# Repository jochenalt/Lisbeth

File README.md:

# Lisbeth
Walter is a self-made, dangerous, industrial robot with 6 DOF. Right in the middle of development. Check the [Documentation](http://walter.readthedocs.io). Contact me via the [hackaday page](https://hackaday.io/post/53678).

### Contents
    /controller  dry theory

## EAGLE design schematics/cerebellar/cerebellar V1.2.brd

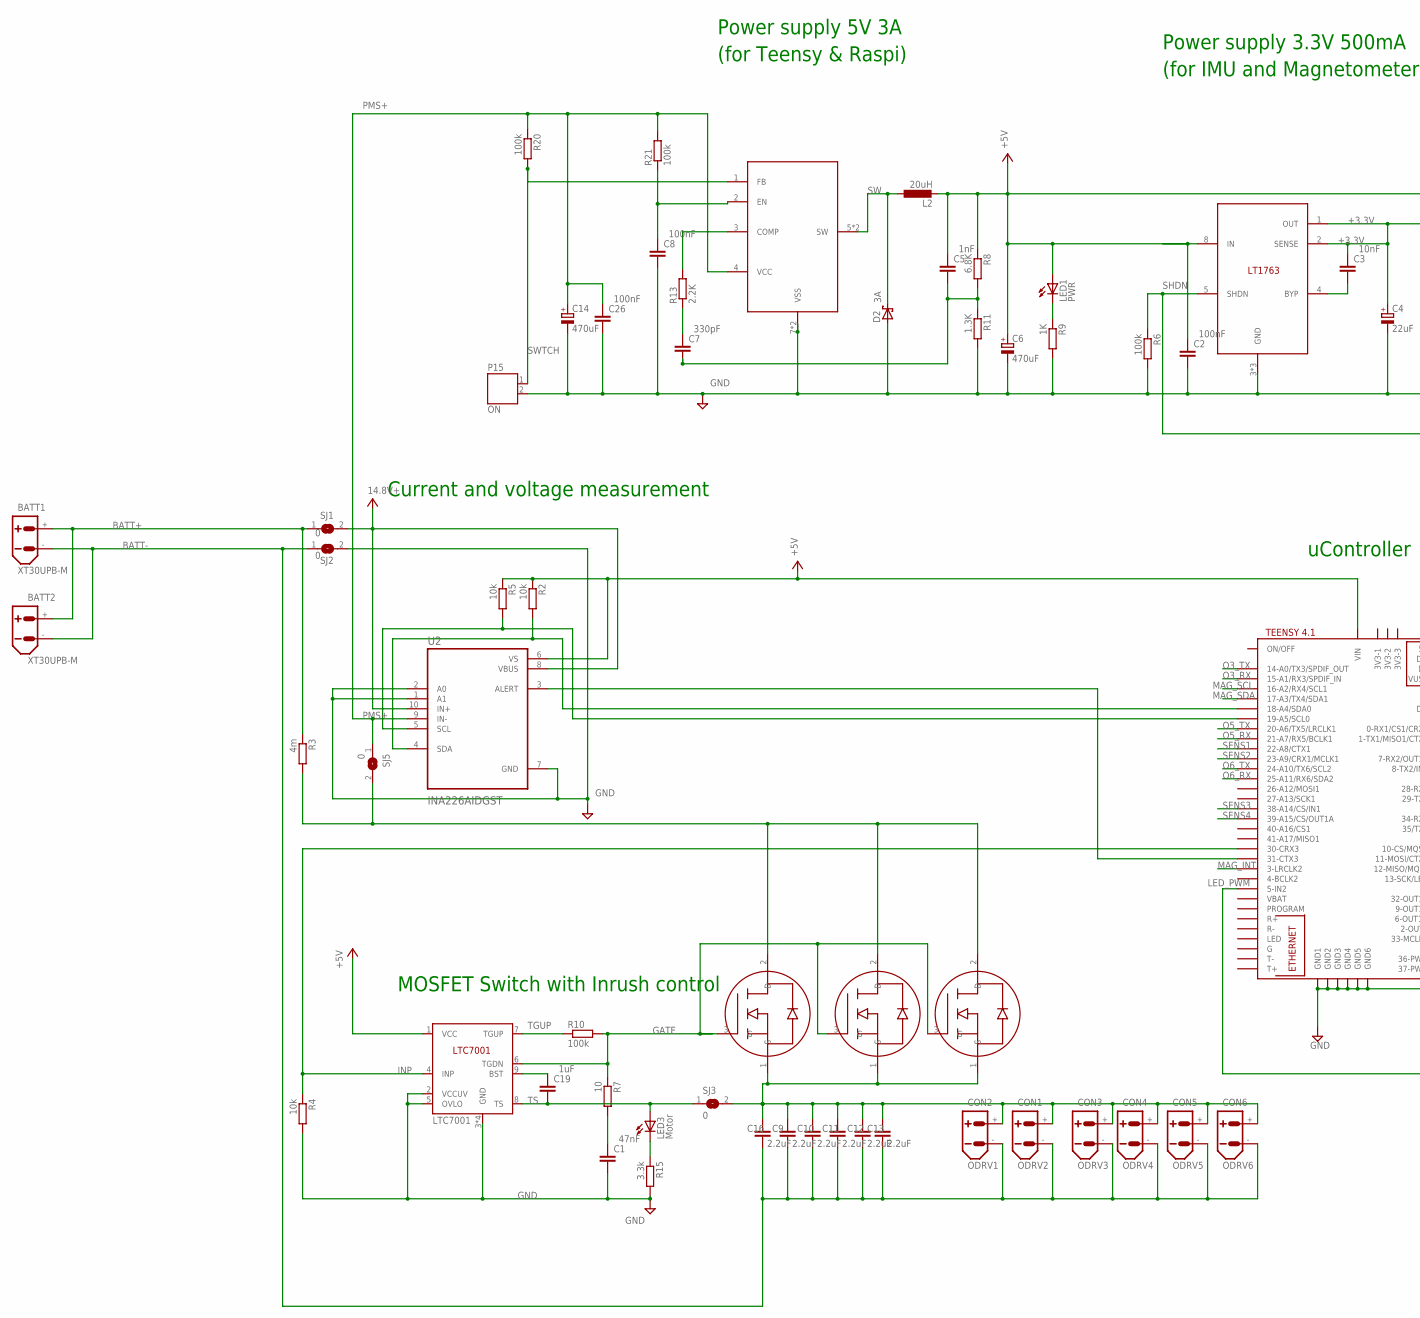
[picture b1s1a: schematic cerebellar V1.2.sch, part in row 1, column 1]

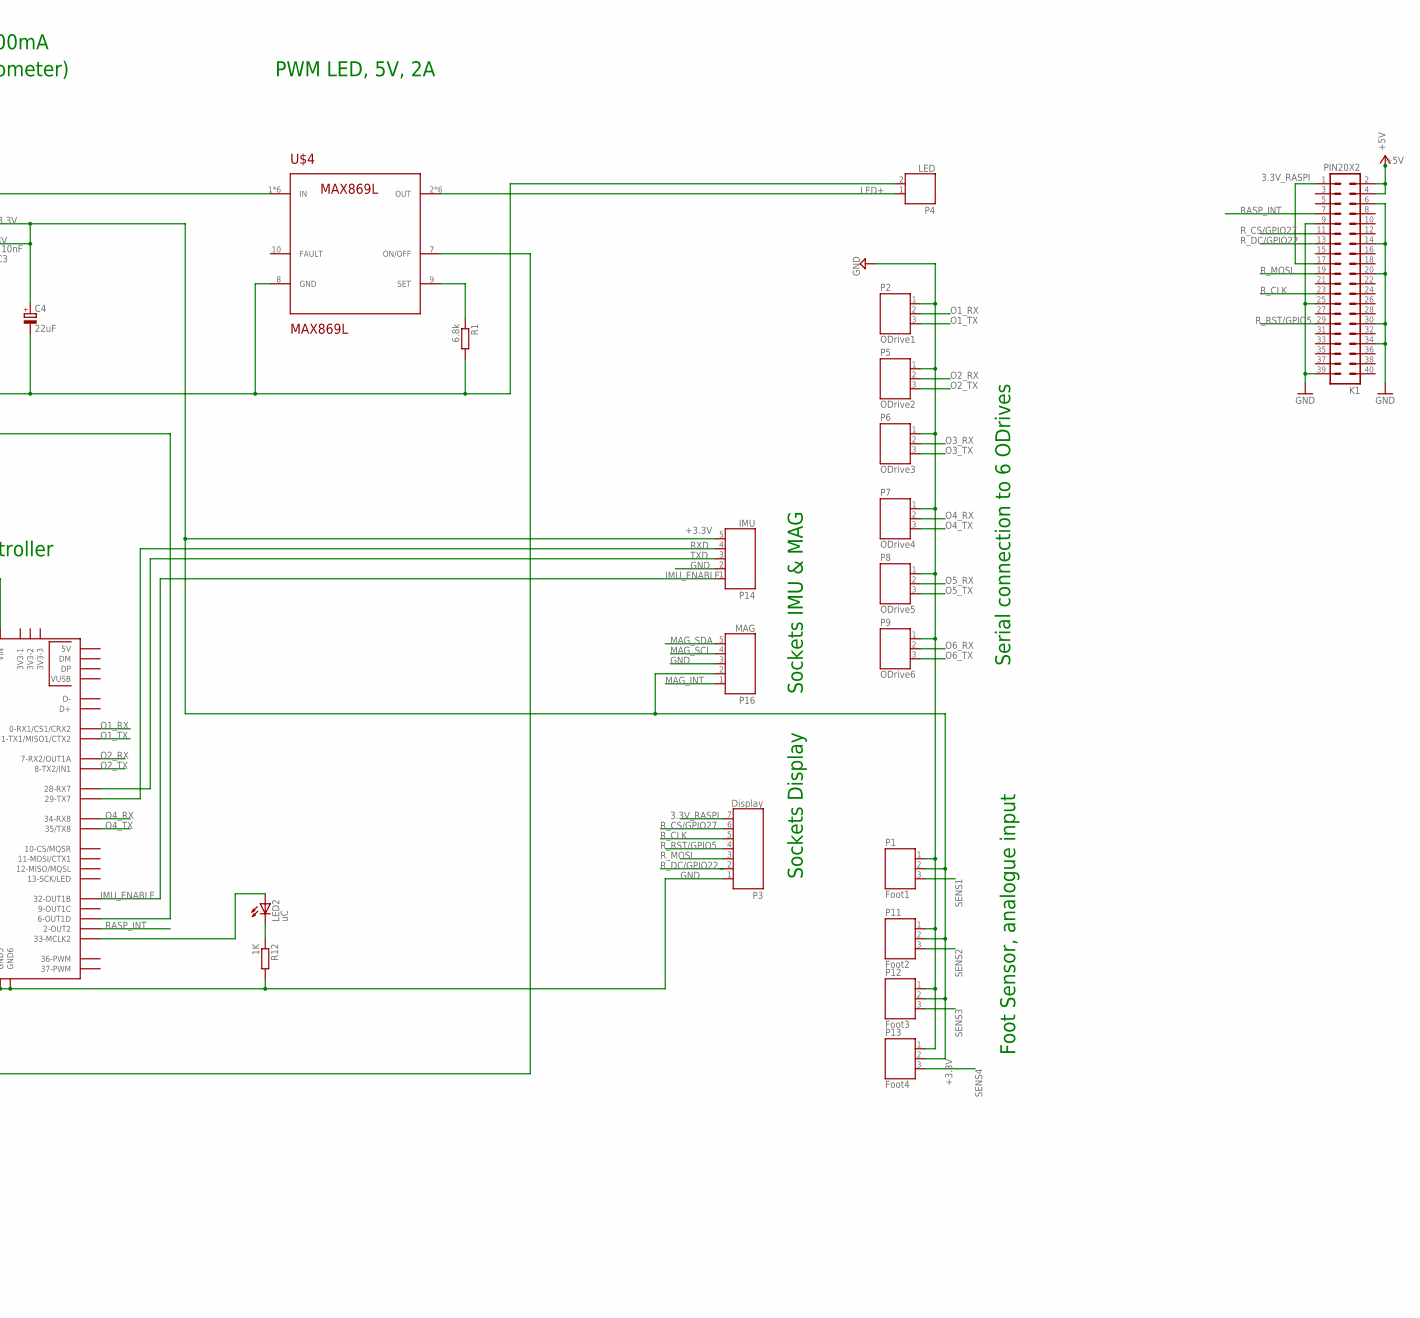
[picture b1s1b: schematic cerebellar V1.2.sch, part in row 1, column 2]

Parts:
BATT1, BATT2: XT30UPB-M
C1: 47nF; C050-024X044
C2, C8, C26: 100nF; C050-024X044
C3: 10nF; C050-024X044
C4: 22uF; E2-4
C5: 1nF; C050-024X044
C6, C14: 470uF; E2,5-6
C7: 330pF; C050-024X044
C9, C10, C11, C12, C13, C16: 2.2uF; C050-024X044
C19: 1uF; C050-024X044
CON1: ODRV2; XT30UPB-F
CON2: ODRV1; XT30UPB-F
CON3: ODRV3; XT30UPB-F
CON4: ODRV4; XT30UPB-F
CON5: ODRV5; XT30UPB-F
CON6: ODRV6; XT30UPB-F
D2: 3A; DO41-10
IC3: LTC7001; MSOP10
K1: PIN20X2; PIN_20X2
L2: 20uH; IRF-3
LED1: PWR; LED3MM
LED2: uC; LED3MM
LED3: Motor; LED3MM
P1: Foot1; JST-PH3
P2: ODrive1; JST-PH3
P3: Display; JST-PH7
P4: LED; JST-PH2
P5: ODrive2; JST-PH3
P6: ODrive3; JST-PH3
P7: ODrive4; JST-PH3
P8: ODrive5; JST-PH3
P9: ODrive6; JST-PH3
P11: Foot2; JST-PH3
P12: Foot3; JST-PH3
P13: Foot4; JST-PH3
P14: IMU; JST-PH5
P15: ON; JST-PH2
P16: MAG; JST-PH5
R1: 6.8k; 0204/7
R2, R4, R5: 10k; 0204/7
R3: 4m; R2512; DIGIKEY 541-WSK25124L000FEACT-ND
R6, R10, R20, R21: 100k; 0204/7
R7: 10; 0204/7
R8: 6.8K; 0204/7
R9, R12: 1K; 0204/7
R11: 1.3K; 0204/7
R13: 2.2K; 0204/7
R15: 3.3k; 0204/7
SJ1, SJ2, SJ3, SJ5: 0; SJ
U2: INA226AIDGST; SOP50P490X110-10N
U$1: TEENSY41
U$2, U$3, U$5: IRF2804-BACK; TO-220H-BACK
U$4: MAX869L; TSSOP-16
U$6: TS2509; SO08
U$8: LT1763; SO08

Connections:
3.3V_RASPI: K1.1, K1.17, P3.7
+3.3V: C3.1, C4.+, P1.2, P11.2, P12.2, P13.2, P14.5, P16.2, U$8.1 (OUT), U$8.2 (SENSE)
+5V: C2.1, C5.1, C6.+, IC3.1 (VCC), K1.2, K1.4, L2.2, LED1.A, R2.1, R5.1, R8.1, U2.6 (VS), U$1.VIN, U$4.1 (IN), U$4.4 (IN), U$4.5 (IN), U$4.12 (IN), U$4.13 (IN), U$4.16 (IN), U$8.8 (IN)
BATT+: BATT1.+, BATT2.+, R3.1, SJ1.1
BATT-: BATT1.-, BATT2.-, C9.2, C10.2, C11.2, C12.2, C13.2, C16.2, CON1.-, CON2.-, CON3.-, CON4.-, CON5.-, CON6.-, SJ2.1
DRAIN: R3.2, SJ5.2, U$2.2 (D), U$3.2 (D), U$5.2 (D)
GATE: IC3.6 (TGDN), R7.1, R10.2, U$2.3 (G), U$3.3 (G), U$5.3 (G)
GND: C1.2, C2.2, C4.-, C6.-, C8.2, C14.-, C26.2, D2.A, IC3.2 (VCCUV), IC3.3 (GND), IC3.5 (OVLO), IC3.10 (GND), IC3.11 (GND), IC3.12 (GND), K1.6, K1.9, K1.14, K1.20, K1.25, K1.30, K1.34, K1.39, P1.1, P2.1, P3.1, P4.2, P5.1, P6.1, P7.1, P8.1, P9.1, P11.1, P12.1, P13.1, P14.2, P15.2, P16.3, R1.2, R4.2, R6.2, R9.2, R11.2, R12.2, R15.2, SJ2.2, U2.1 (A1), U2.2 (A0), U2.7 (GND), U$1.GND1, U$1.GND2, U$1.GND3, U$1.GND4, U$1.GND5, U$1.GND6, U$4.8 (GND), U$6.7 (VSS), U$6.8 (VSS), U$8.3 (GND), U$8.6 (GND), U$8.7 (GND)
IMU_ENABLE: P14.1, U$1.32-OUT1B
INP: IC3.4 (INP), R4.1, U$1.30-CRX3
LED+: P4.1, U$4.2 (OUT), U$4.3 (OUT), U$4.6 (OUT), U$4.11 (OUT), U$4.14 (OUT), U$4.15 (OUT)
LED_PWM: U$1.5-IN2, U$4.7 (ON/OFF)
MAG_INT: P16.1, U$1.3-LRCLK2
MAG_SCL: P16.4, U$1.16-A2/RX4/SCL1
MAG_SDA: P16.5, U$1.17-A3/TX4/SDA1
unnamed: C1.1, R7.2
unnamed: R1.1, U$4.9 (SET)
unnamed: LED2.K (C), R12.1
unnamed: LED2.A, U$1.33-MCLK2
unnamed: U2.3 (ALERT), U$1.31-CTX3
unnamed: C5.2, C7.2, R8.2, R11.1
unnamed: C3.2, U$8.4 (BYP)
unnamed: R13.2, U$6.3 (COMP)
unnamed: C7.1, R13.1
unnamed: R5.2, U2.5 (SCL), U$1.19-A5/SCL0
unnamed: R2.2, U2.4 (SDA), U$1.18-A4/SDA0
unnamed: C19.1, IC3.9 (BST)
unnamed: LED3.K (C), R15.1
unnamed: LED1.K (C), R9.1
unnamed: C8.1, R21.1, U$6.2 (EN)
O1_RX: P2.2, U$1.0-RX1/CS1/CRX2
O1_TX: P2.3, U$1.1-TX1/MISO1/CTX2
O2_RX: P5.2, U$1.7-RX2/OUT1A
O2_TX: P5.3, U$1.8-TX2/IN1
O3_RX: P6.2, U$1.15-A1/RX3/SPDIF_IN
O3_TX: P6.3, U$1.14-A0/TX3/SPDIF_OUT
O4_RX: P7.2, U$1.34-RX8
O4_TX: P7.3, U$1.35-TX8 (35/TX8)
O5_RX: P8.2, U$1.21-A7/RX5/BCLK1
O5_TX: P8.3, U$1.20-A6/TX5/LRCLK1
O6_RX: P9.2, U$1.25-A11/RX6/SDA2
O6_TX: P9.3, U$1.24-A10/TX6/SCL2
PMS+: C14.+, C26.1, R20.1, R21.2, SJ5.1, U2.9 (IN-), U$6.4 (VCC)
POWER+: C9.1, C10.1, C11.1, C12.1, C13.1, C16.1, CON1.+, CON2.+, CON3.+, CON4.+, CON5.+, CON6.+, SJ3.2, U$2.1 (S), U$3.1 (S), U$5.1 (S)
RASP_INT: K1.7, U$1.2-OUT2
RXD: P14.4, U$1.29-TX7
R_CLK: K1.23, P3.5
R_CS/GPIO27: K1.11, P3.6
R_DC/GPIO22: K1.13, P3.2
R_MOSI: K1.19, P3.3
R_RST/GPIO5: K1.29, P3.4
SENS1: P1.3, U$1.22-A8/CTX1
SENS2: P11.3, U$1.23-A9/CRX1/MCLK1
SENS3: P12.3, U$1.38-A14/CS/IN1
SENS4: P13.3, U$1.39-A15/CS/OUT1A
SHDN: R6.1, U$1.6-OUT1D, U$8.5 (SHDN)
SW: D2.C, L2.1, U$6.5 (SW), U$6.6 (SW)
SWTCH: P15.1, R20.2, U$6.1 (FB)
TGUP: IC3.7 (TGUP), R10.1
TS: C19.2, IC3.8 (TS), LED3.A, SJ3.1
TXD: P14.3, U$1.28-RX7
V+: SJ1.2, U2.8 (VBUS), U2.10 (IN+)

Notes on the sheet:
Foot Sensor, analogue input
Serial connection to 6 ODrives
Power supply 5V 3A (for Teensy & Raspi)
Current and voltage measurement
MOSFET Switch with Inrush control
uController
PWM LED, 5V, 2A
Power supply 3.3V 500mA (for IMU and Magnetometer)
Sockets IMU & MAG
Sockets Display

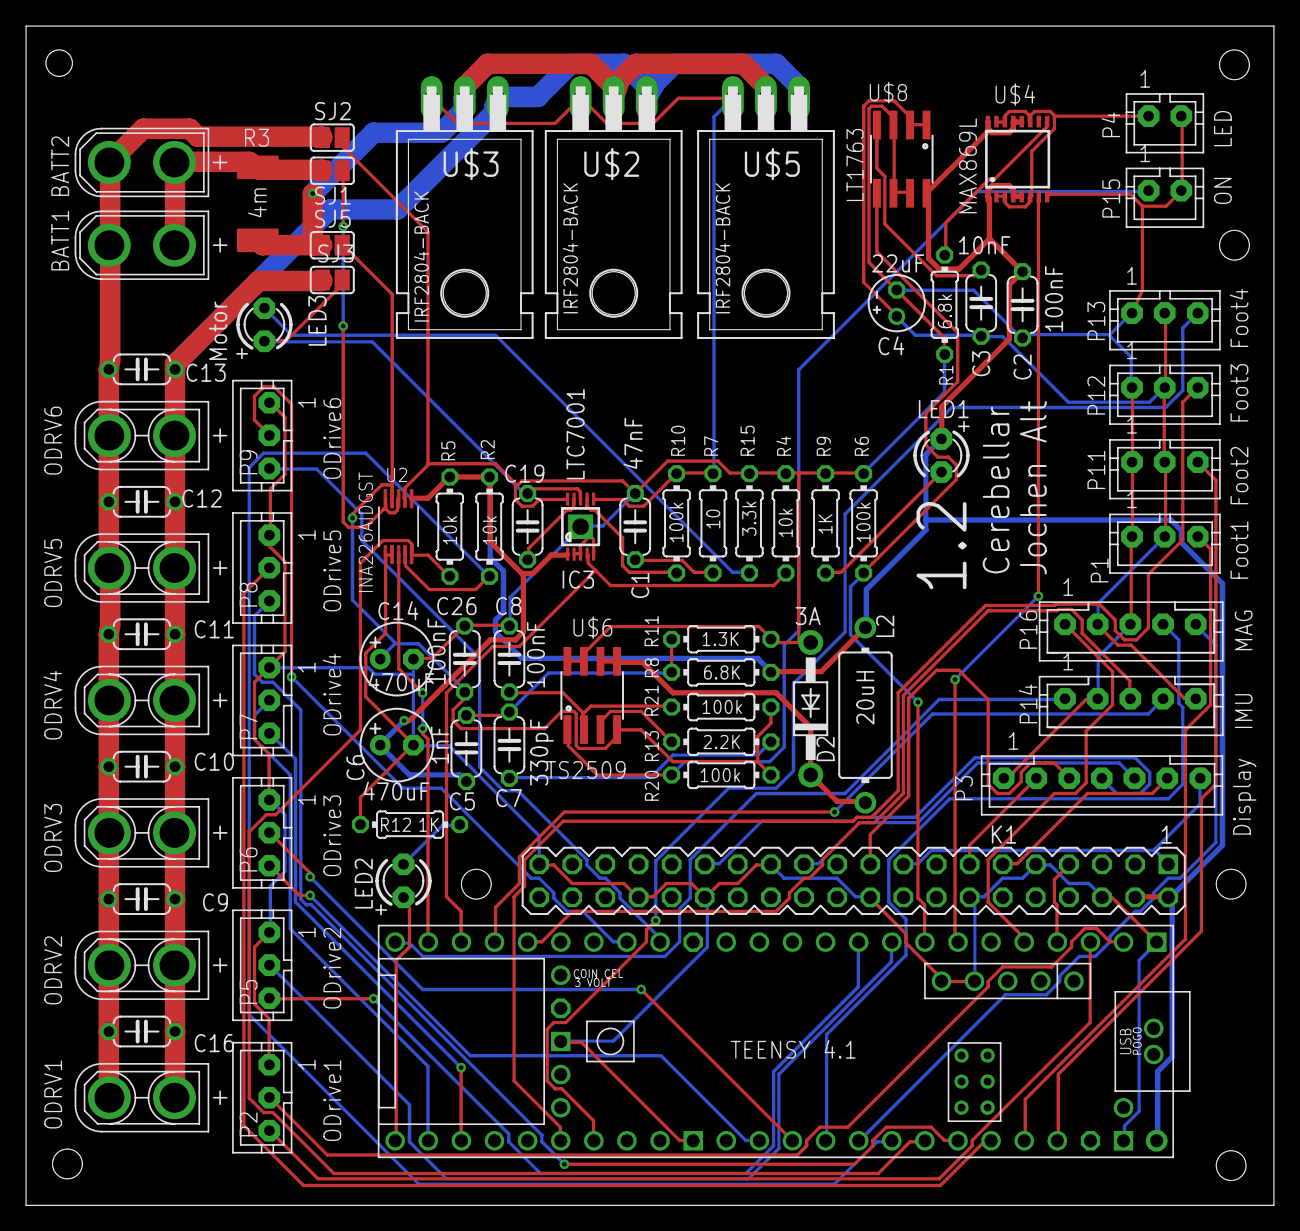
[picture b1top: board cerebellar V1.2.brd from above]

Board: 2 copper layers, 95.7 x 90.5 mm, 75 parts (0 on the bottom side), 62 nets.

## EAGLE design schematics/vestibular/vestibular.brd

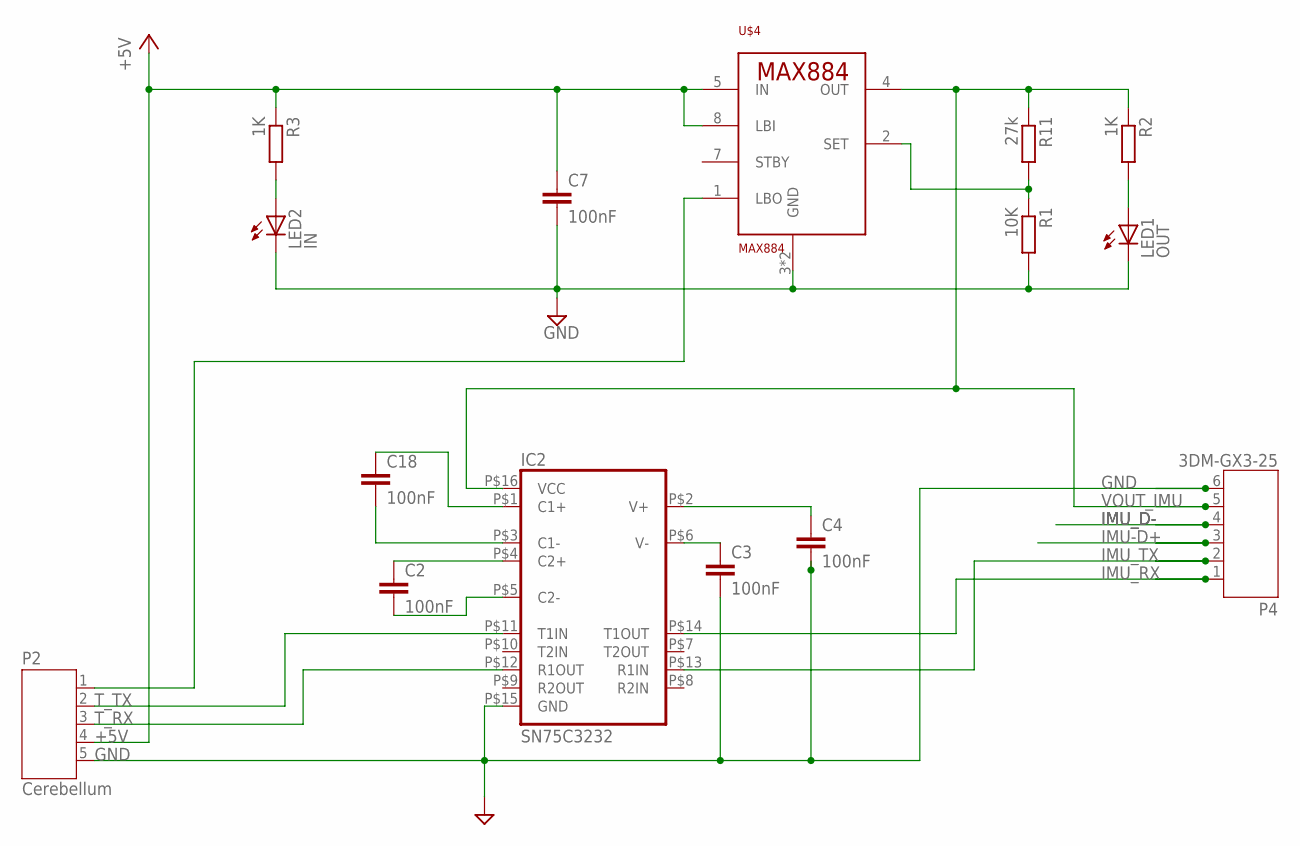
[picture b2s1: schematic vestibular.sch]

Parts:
C2, C3, C4, C7, C18: 100nF; C025-025X050
IC2: SN75C3232; SOIC16
LED1: OUT; LED3MM
LED2: IN; LED3MM
P2: Cerebellum; JST-PH5
P4: 3DM-GX3-25; JST-PH6
R1: 10K; 0204/7
R2, R3: 1K; 0204/7
R11: 27k; 0204/7
U$4: MAX884; SO08

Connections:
+5V: C7.1, P2.4, R3.1, U$4.5 (IN), U$4.8 (LBI)
GND: C3.2, C4.2, C7.2, IC2.P$15 (GND), LED1.K (C), LED2.K (C), P2.5, P4.6, R1.2, U$4.3 (GND), U$4.6 (GND)
IMU-D+: P4.3
IMU_D-: P4.4
IMU_RX: IC2.P$14 (T1OUT), P4.1
IMU_TX: IC2.P$13 (R1IN), P4.2
unnamed: LED1.A, R2.2
unnamed: LED2.A, R3.2
unnamed: C18.1, IC2.P$1 (C1+)
unnamed: P2.1, U$4.1 (LBO)
unnamed: C18.2, IC2.P$3 (C1-)
unnamed: R1.1, R11.2, U$4.2 (SET)
unnamed: C2.1, IC2.P$4 (C2+)
unnamed: C2.2, IC2.P$5 (C2-)
unnamed: C4.1, IC2.P$2 (V+)
unnamed: C3.1, IC2.P$6 (V-)
T_RX: IC2.P$12 (R1OUT), P2.3
T_TX: IC2.P$11 (T1IN), P2.2
VOUT_IMU: IC2.P$16 (VCC), P4.5, R2.1, R11.1, U$4.4 (OUT)

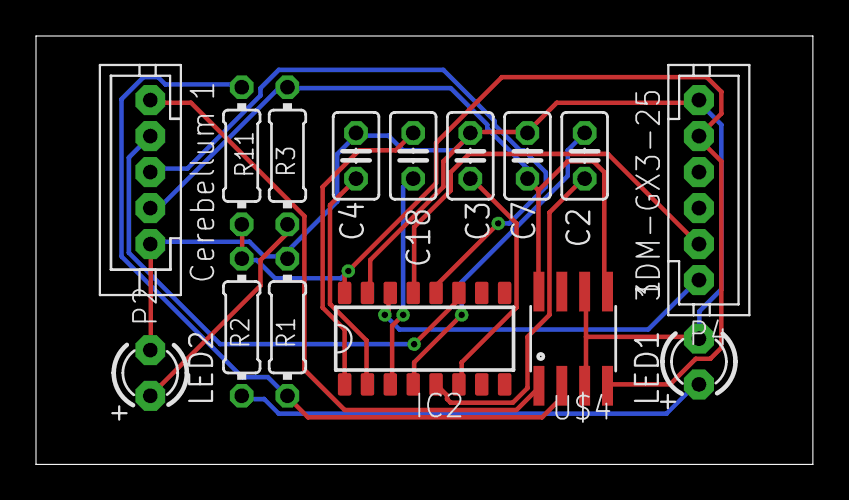
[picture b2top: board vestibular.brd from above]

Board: 2 copper layers, 43.2 x 23.8 mm, 15 parts (0 on the bottom side), 17 nets.

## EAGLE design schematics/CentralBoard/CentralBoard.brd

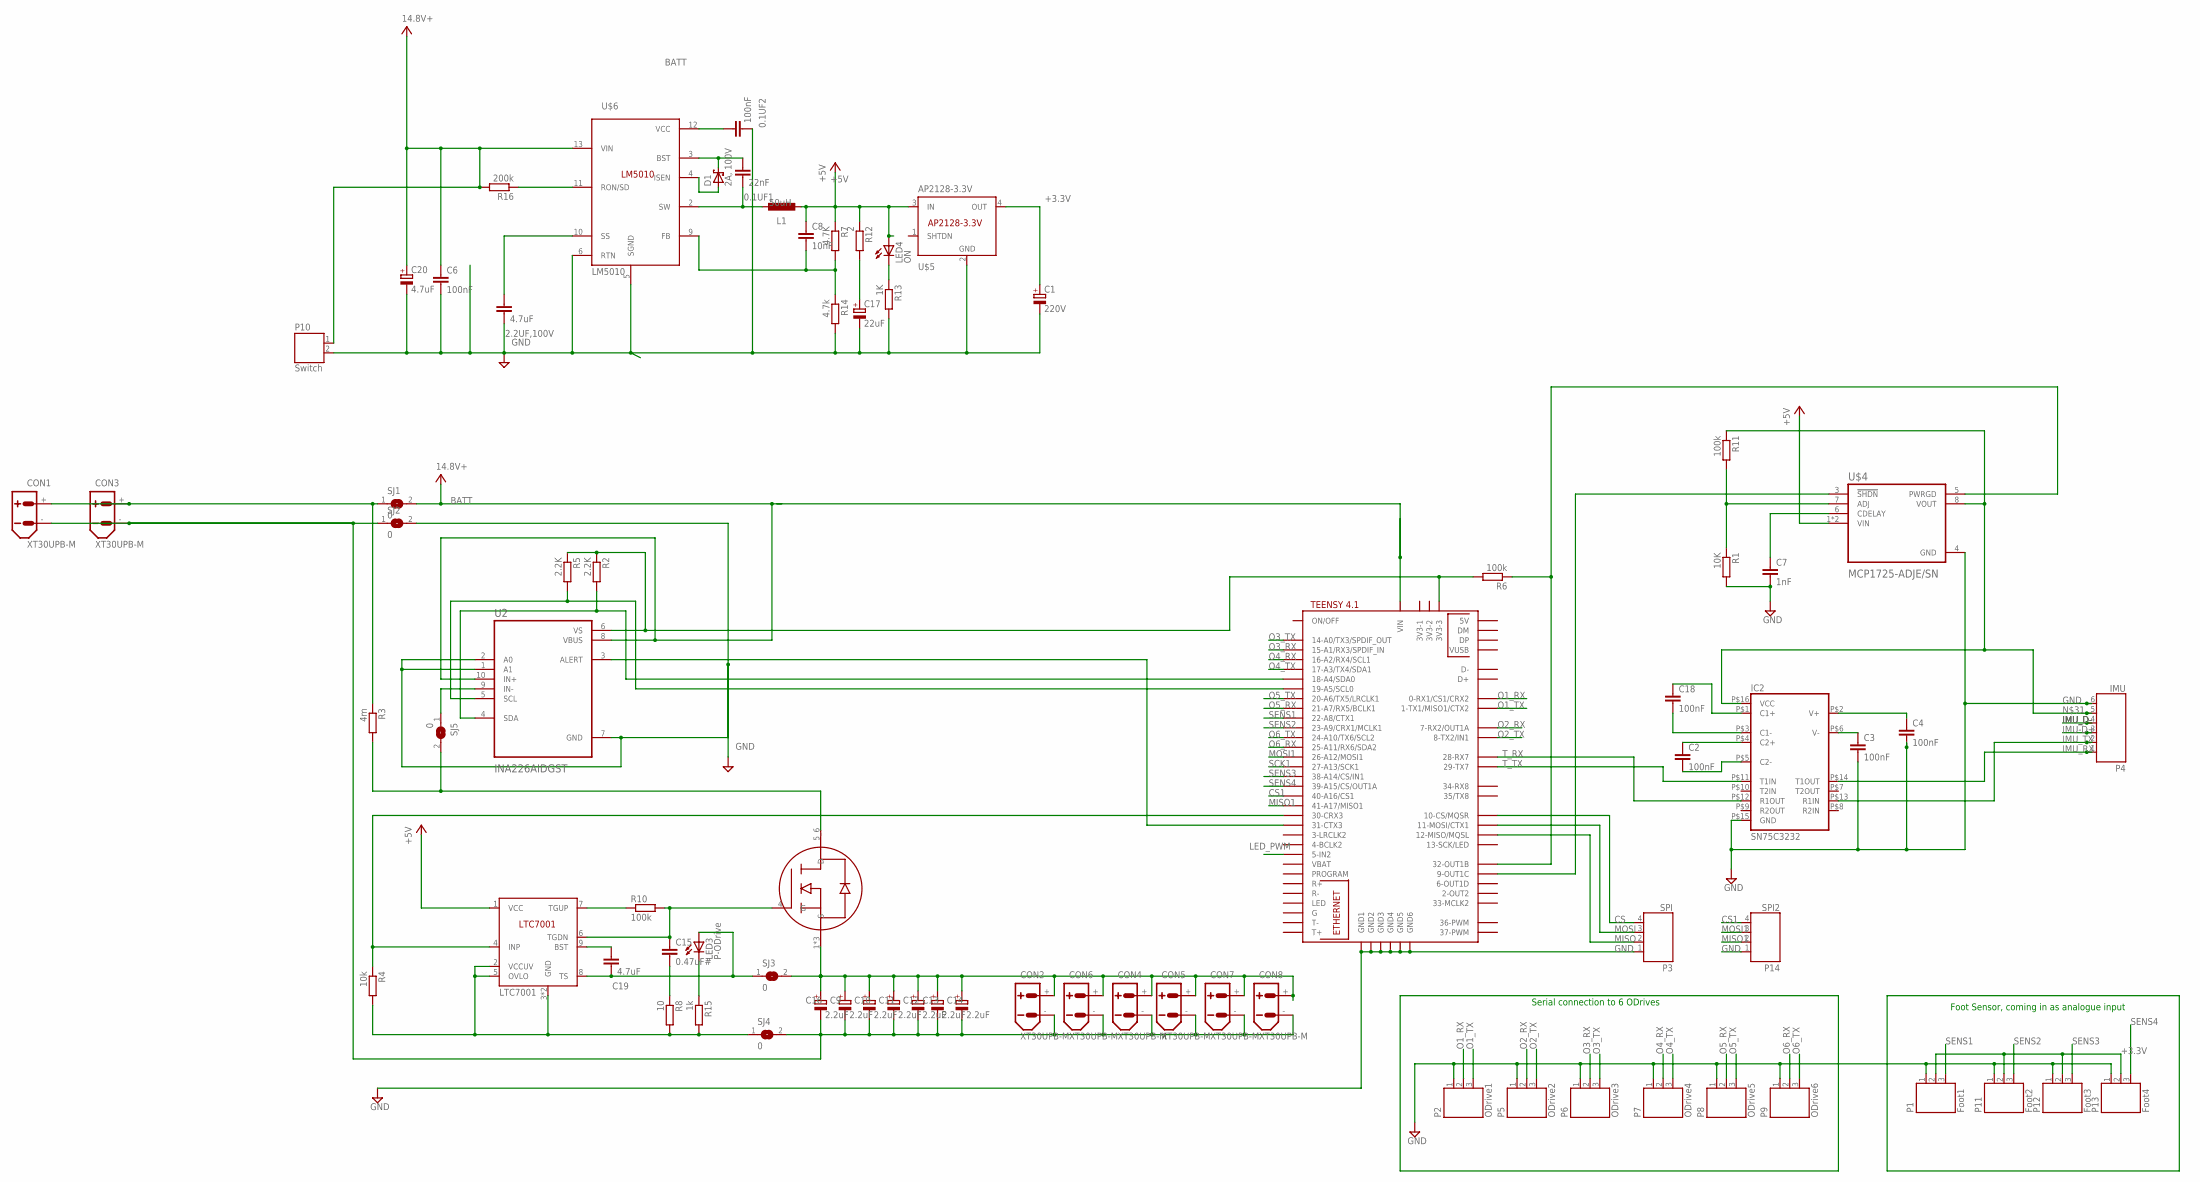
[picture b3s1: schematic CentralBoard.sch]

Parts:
0.1UF1: 22nF; C025-025X050
0.1UF2: 100nF; C025-025X050
2.2UF,100V: 4.7uF; C025-025X050
C1: 220V; E2,5-7
C2, C3, C4, C6, C18: 100nF; C025-025X050
C7: 1nF; C025-025X050
C8: 10nF; C025-025X050
C9, C10, C11, C12, C13, C14, C16: 2.2uF; E2-5
C15: 0.47uF#; C025-025X050
C17: 22uF; E2-4
C19: 4.7uF; C025-025X050
C20: 4.7uF; E2-4
CON1, CON2, CON3, CON4, CON5, CON6, CON7, CON8: XT30UPB-M
D1: 2A, 100V; DO41-10
IC2: SN75C3232; SOIC16
IC3: LTC7001; MSOP10
L1: 50uH; 0204/5
LED3: P-ODrive; LED3MM
LED4: ON; LED3MM
P1: Foot1; JST-PH3
P2: ODrive1; JST-PH3
P3: SPI; JST-PH4
P4: IMU; JST-PH6
P5: ODrive2; JST-PH3
P6: ODrive3; JST-PH3
P7: ODrive4; JST-PH3
P8: ODrive5; JST-PH3
P9: ODrive6; JST-PH3
P10: Switch; JST-PH2
P11: Foot2; JST-PH3
P12: Foot3; JST-PH3
P13: Foot4; JST-PH3
P14: SPI2; JST-PH4
R1: 10K; 0204/7
R2, R5: 2.2K; 0204/7
R3: 4m; R2512; DIGIKEY 541-WSK25124L000FEACT-ND
R4: 10k; 0204/7
R6, R10, R11: 100k; 0204/7
R7: 4.7K; 0204/7
R8: 10; 0204/7
R12: 2; 0204/7
R13: 1K; 0204/7
R14: 4.7k; 0204/7
R15: 1k; 0204/7
R16: 200k; 0204/7
SJ1, SJ2, SJ3, SJ4, SJ5: 0; SJ
U2: INA226AIDGST; SOP50P490X110-10N
U$1: TEENSY41
U$2: DMTH8003SPS; DIO_NTS1045EMFST1G
U$4: MCP1725-ADJE/SN; SOIC127P599X175-8N
U$5: AP2128-3.3V; SOT-23-5
U$6: LM5010; TSSOP-14

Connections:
+3.3V: C1.+, P1.2, P11.2, P12.2, P13.2, U$5.4 (OUT)
+5V: C8.1, IC3.1 (VCC), L1.2, LED4.A, R7.1, R12.1, U$4.1 (VIN), U$4.2 (VIN), U$5.3 (IN)
BATT: C6.1, C20.+, P10.1, R16.2, SJ1.2, U2.8 (VBUS), U2.10 (IN+), U$6.13 (VIN)
BATT+: CON1.+, CON3.+, R3.1, SJ1.1
BATT-: C9.-, C10.-, C11.-, C12.-, C13.-, C14.-, C16.-, CON1.-, CON2.-, CON3.-, CON4.-, CON5.-, CON6.-, CON7.-, CON8.-, SJ2.1, SJ4.2
CS: P3.4, U$1.10-CS\MQSR (10-CS/MQSR)
CS1: P14.4, U$1.40-A16/CS1
GND: 0.1UF2.2, 2.2UF,100V.2, C1.-, C3.2, C4.2, C6.2, C7.2, C17.-, C20.-, IC2.P$15 (GND), P1.1, P2.1, P3.1, P4.6, P5.1, P6.1, P7.1, P8.1, P9.1, P10.2, P11.1, P12.1, P13.1, P14.1, R1.2, R13.2, R14.2, SJ2.2, U2.1 (A1), U2.2 (A0), U2.7 (GND), U$1.GND1, U$1.GND2, U$1.GND3, U$1.GND4, U$1.GND5, U$1.GND6, U$4.4 (GND), U$5.2 (GND), U$6.5 (SGND), U$6.6 (RTN)
IMU-D+: P4.3
IMU_D-: P4.4
IMU_RX: IC2.P$14 (T1OUT), P4.1
IMU_TX: IC2.P$13 (R1IN), P4.2
IMU_VDD: R6.1, U$1.32-OUT1B, U$4.5 (PWRGD)
LED_PWM: U$1.5-IN2
MISO: P3.2, U$1.12-MISO/MQSL
MISO1: P14.2, U$1.41-A17/MISO1
MOSI: P3.3, U$1.11-MOSI/CTX1
MOSI1: P14.3, U$1.26-A12/MOSI1
unnamed: LED4.K (C), R13.1
unnamed: C7.1, U$4.6 (CDELAY)
unnamed: IC3.7 (TGUP), R10.1
unnamed: U2.3 (ALERT), U$1.31-CTX3
unnamed: C18.1, IC2.P$1 (C1+)
unnamed: U$1.9-OUT1C, U$4.3 (!SHDN)
unnamed: C18.2, IC2.P$3 (C1-)
unnamed: R3.2, SJ5.2, U$2.5_6 (D)
unnamed: IC3.4 (INP), R4.1, U$1.30-CRX3
unnamed: C2.1, IC2.P$4 (C2+)
unnamed: C2.2, IC2.P$5 (C2-)
unnamed: C4.1, IC2.P$2 (V+)
unnamed: C3.1, IC2.P$6 (V-)
unnamed: IC3.2 (VCCUV), IC3.3 (GND), IC3.5 (OVLO), IC3.11 (GND), R4.2, R8.2, R15.2, SJ4.1
unnamed: C15.2, R8.1
unnamed: R5.2, U2.5 (SCL), U$1.19-A5/SCL0
unnamed: SJ5.1, U2.9 (IN-)
unnamed: C15.1, IC3.6 (TGDN), R10.2, U$2.4 (G)
unnamed: C17.+, R12.2
unnamed: C9.+, C10.+, C11.+, C12.+, C13.+, C14.+, C16.+, CON2.+, CON4.+, CON5.+, CON6.+, CON7.+, CON8.+, SJ3.2, U$2.1 (S), U$2.2 (S), U$2.3 (S)
unnamed: R2.2, U2.4 (SDA), U$1.18-A4/SDA0
unnamed: R2.1, R5.1, R6.2, U2.6 (VS), U$1.3V3-3
unnamed: C19.1, IC3.9 (BST)
unnamed: R1.1, R11.2, U$4.7 (ADJ)
unnamed: C19.2, IC3.8 (TS), LED3.A, SJ3.1
unnamed: R16.1, U$6.11 (RON/SD)
unnamed: 0.1UF1.1, D1.C, U$6.3 (BST)
unnamed: LED3.K (C), R15.1
unnamed: IC2.P$16 (VCC), P4.5, R11.1, U$4.8 (VOUT)
unnamed: 2.2UF,100V.1, U$6.10 (SS)
unnamed: 0.1UF2.1, U$6.12 (VCC)
unnamed: 0.1UF1.2, L1.1, U$6.2 (SW)
unnamed: C8.2, R7.2, R14.1, U$6.9 (FB)
unnamed: D1.A, U$6.4 (ISEN)
O1_RX: P2.2, U$1.0-RX1/CS1/CRX2
O1_TX: P2.3, U$1.1-TX1/MISO1/CTX2
O2_RX: P5.2, U$1.7-RX2/OUT1A
O2_TX: P5.3, U$1.8-TX2/IN1
O3_RX: P6.2, U$1.15-A1/RX3/SPDIF_IN
O3_TX: P6.3, U$1.14-A0/TX3/SPDIF_OUT
O4_RX: P7.2, U$1.16-A2/RX4/SCL1
O4_TX: P7.3, U$1.17-A3/TX4/SDA1
O5_RX: P8.2, U$1.21-A7/RX5/BCLK1
O5_TX: P8.3, U$1.20-A6/TX5/LRCLK1
O6_RX: P9.2, U$1.25-A11/RX6/SDA2
O6_TX: P9.3, U$1.24-A10/TX6/SCL2
SCK1: U$1.27-A13/SCK1
SENS1: P1.3, U$1.22-A8/CTX1
SENS2: P11.3, U$1.23-A9/CRX1/MCLK1
SENS3: P12.3, U$1.38-A14/CS/IN1
SENS4: P13.3, U$1.39-A15/CS/OUT1A
T_RX: IC2.P$12 (R1OUT), U$1.28-RX7
T_TX: IC2.P$11 (T1IN), U$1.29-TX7

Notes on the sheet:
Foot Sensor, coming in as analogue input
Serial connection to 6 ODrives

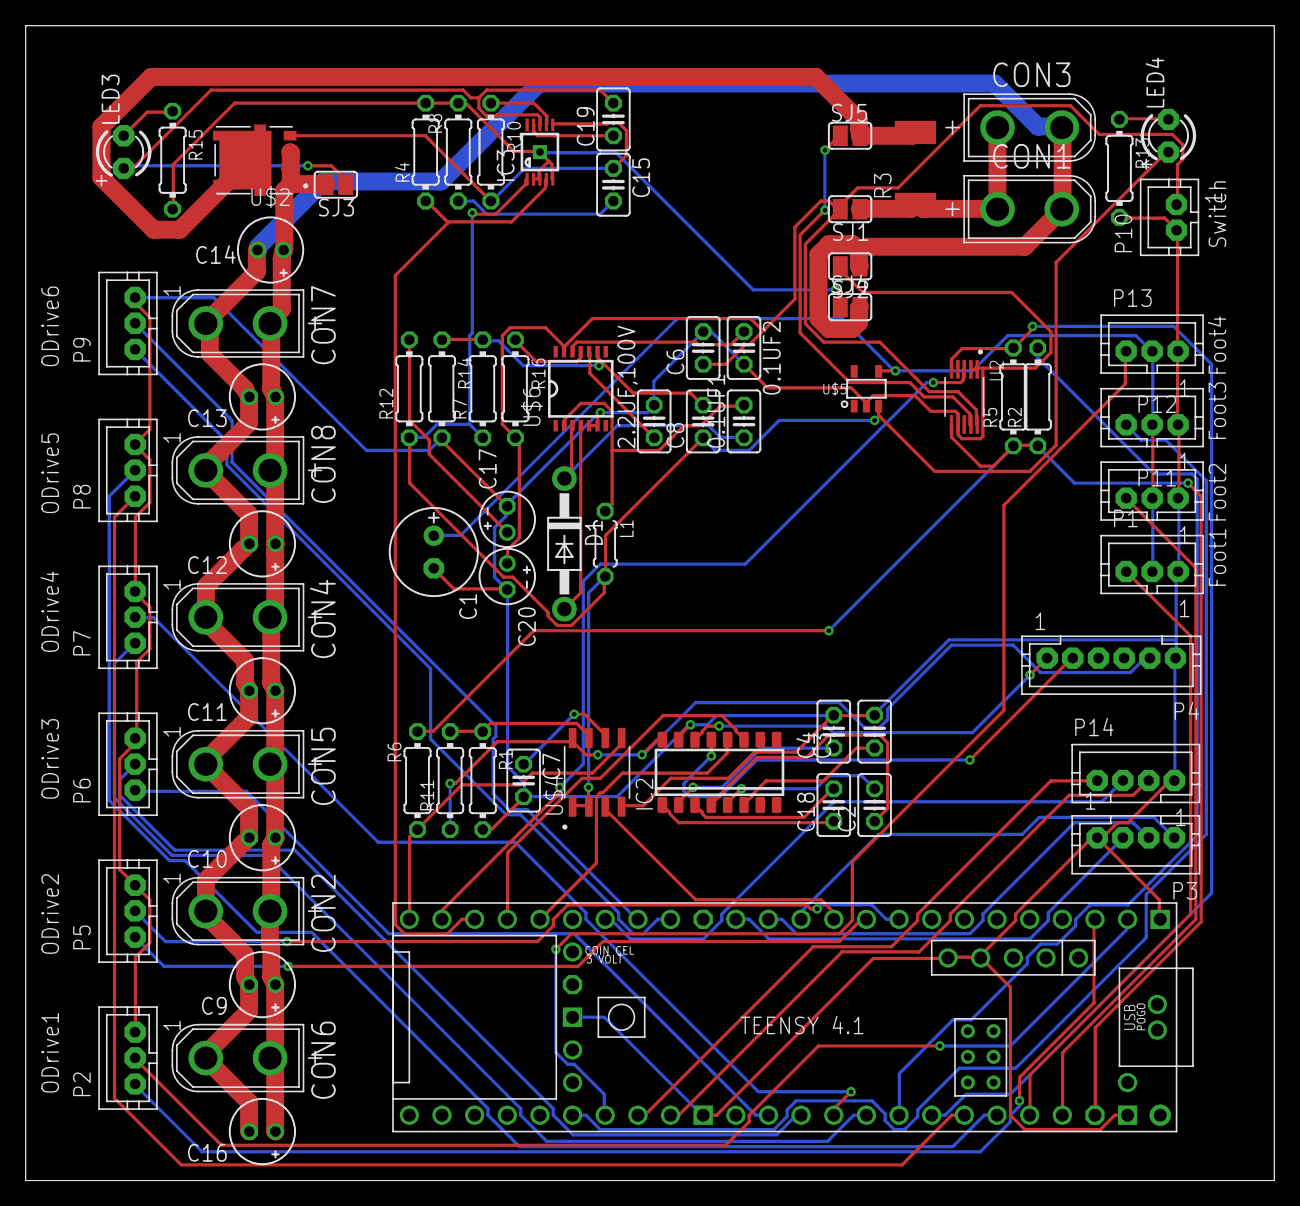
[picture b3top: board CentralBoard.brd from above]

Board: 2 copper layers, 97.1 x 89.8 mm, 76 parts (0 on the bottom side), 67 nets.

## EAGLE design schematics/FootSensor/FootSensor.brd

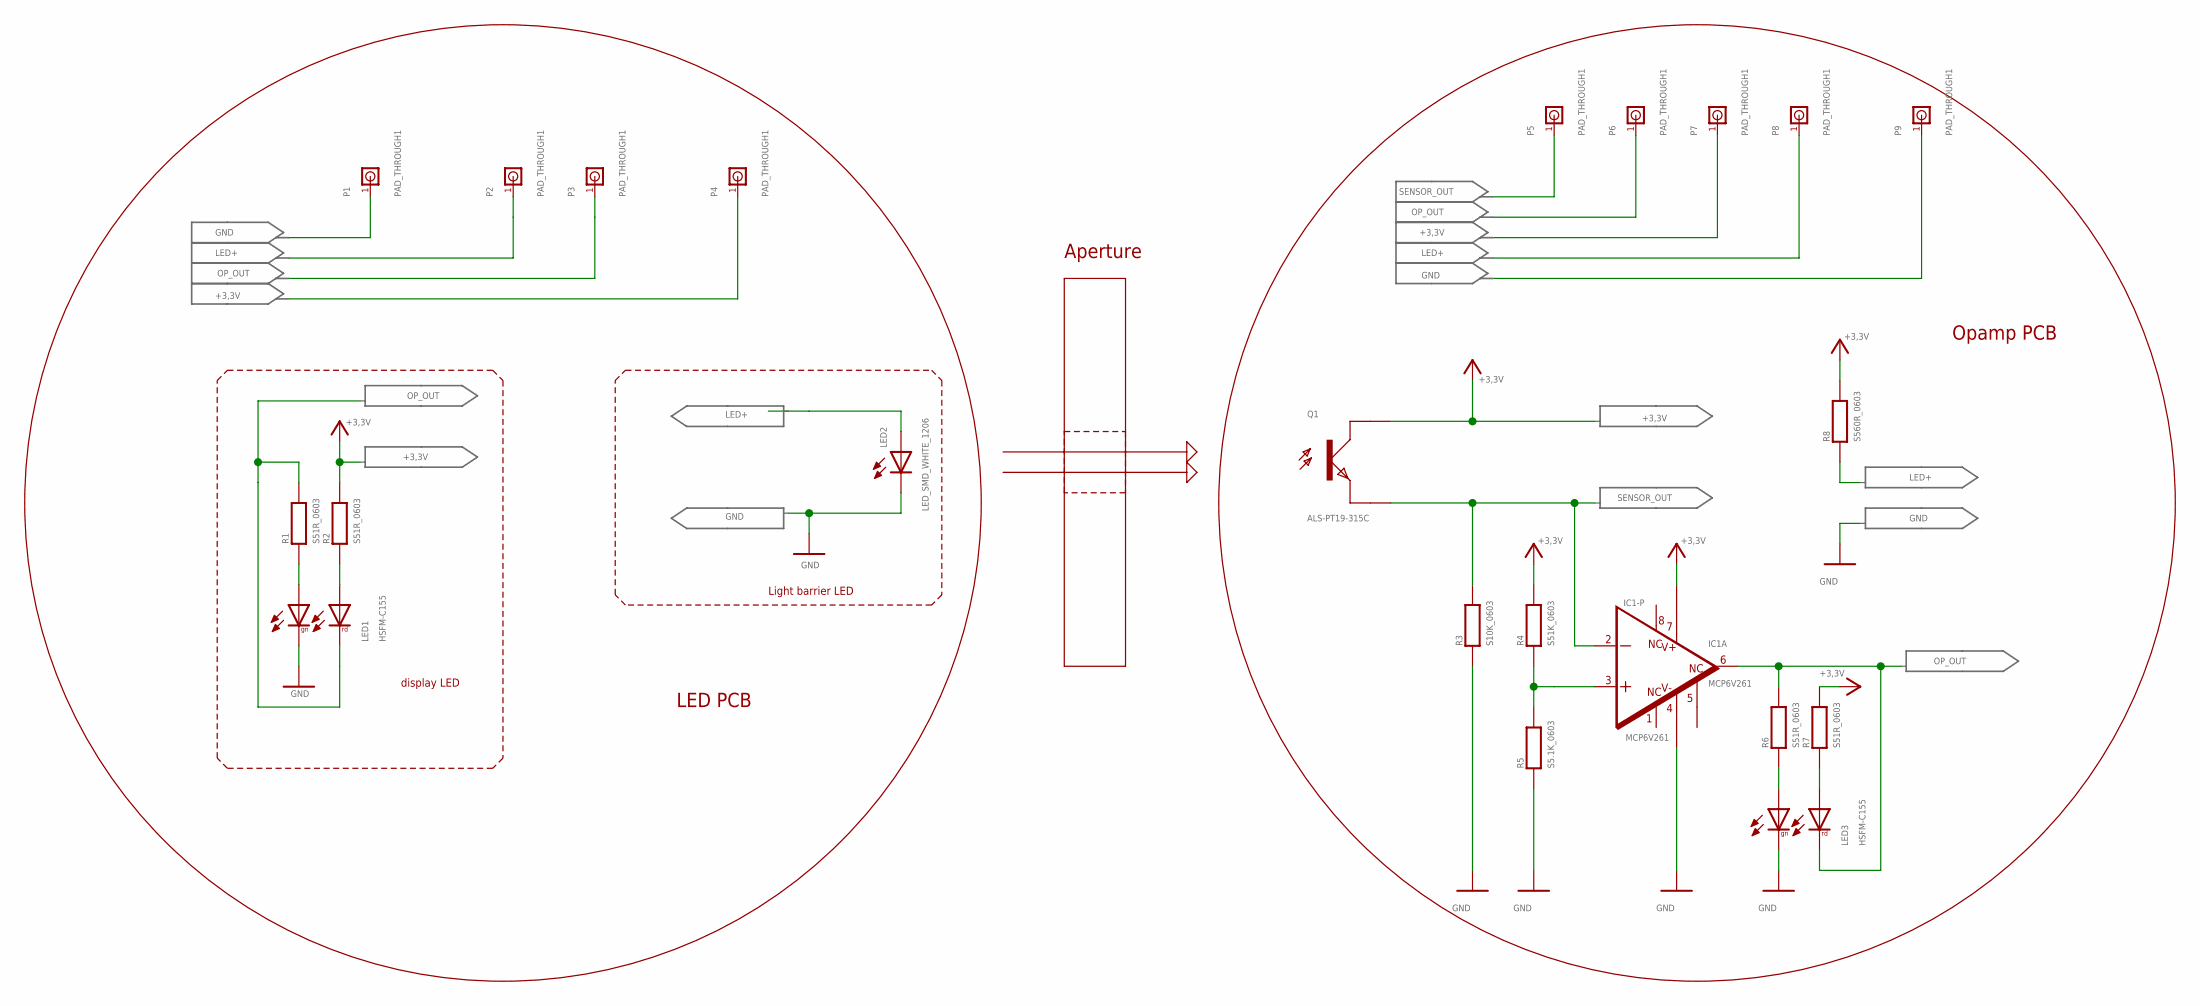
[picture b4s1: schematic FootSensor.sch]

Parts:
IC1: MCP6V261; MSOP8
LED1, LED3: HSFM-C155; 3225
LED2: LED_SMD_WHITE_1206; 1206C
P1, P2, P3, P4, P5, P6, P7, P8, P9: PAD_THROUGH1; PAD_TH_056X055
Q1: ALS-PT19-315C; FOTOTRANSISTOR
R1, R2, R6, R7: S51R_0603; 0603R
R3: S10K_0603; 0603R
R4: S51K_0603; 0603R
R5: S5.1K_0603; 0603R
R8: S560R_0603; 0603R

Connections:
+3,3V: IC1.7, P4.P$1, P7.P$1, Q1.1 (C), R2.P$2 (2), R4.P$2 (2), R7.P$2 (2), R8.P$2 (2)
GND: IC1.4, LED1.2, LED2.- (C1), LED3.2, P1.P$1, P9.P$1, R3.P$1 (1), R5.P$1 (1)
LED+: LED2.+ (A1), P2.P$1, P8.P$1, R8.P$1 (1)
unnamed: IC1.3, R4.P$1 (1), R5.P$2 (2)
unnamed: LED3.1, R6.P$1 (1)
unnamed: LED3.3, R7.P$1 (1)
unnamed: LED1.1, R1.P$1 (1)
unnamed: LED1.3, R2.P$1 (1)
OP_OUT: IC1.6, LED1.4, LED3.4, P3.P$1, P6.P$1, R1.P$2 (2), R6.P$2 (2)
SENSOR_OUT: IC1.2, P5.P$1, Q1.2 (E), R3.P$2 (2)

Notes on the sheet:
Aperture
LED PCB
Opamp PCB
display LED
Light barrier LED

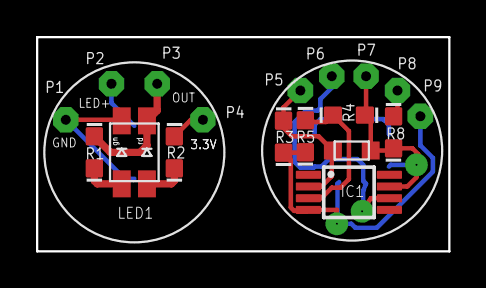
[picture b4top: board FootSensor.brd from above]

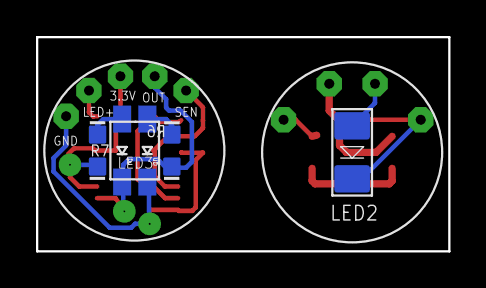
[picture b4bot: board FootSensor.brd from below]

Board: 2 copper layers, 22.9 x 11.9 mm, 22 parts (4 on the bottom side), 10 nets.

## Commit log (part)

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2022-06-13 Externalizes QPWBC Wrapper
2022-06-13 introduced InvKin.initialize
2022-06-13 additional types
2022-06-16 removed InvKin.py and replaced by C++ code
2022-06-16 reduced size of qdes and vdes
2022-06-16 prepare C++ WBC
2022-06-16 validation for correctness for c++ WBC
2022-06-17 divided Python wrappers
2022-06-17 replaced QP_WBC with C++
2022-06-17 changed signature
2022-06-17 introduced wbcwrapper
2022-06-17 replace Controller params by class
2022-06-17 replace estimator initialize parameter
2022-06-17 parameter for MPC
2022-06-17 introduced compensation of ff
2022-06-17 cleanup
2022-06-17 initialised via q_init
2022-06-17 prep
2022-06-17 bugfix in Estimator: update_state is called now
2022-06-17 removed stuff
2022-06-17 aligned array size
2022-06-17 intermediate state
2022-06-18 q_wbc contains RPY instead of Quaternion now
2022-06-18 removed need for q in Gait
2022-06-18 used RPY instead of Quaternions in controller.q
2022-06-18 made self.q with RPY instead of quaternions
2022-06-18 changed layout of v_ref
2022-06-18 new class Filter
2022-06-18 prepare
2022-06-18 added MpcWrapper
2022-06-18 prepared MpcWrapper
2022-06-18 created MpcController
2022-06-19 new Matrix type
2022-06-19 improved initialisation of MPC
2022-06-19 introduced Python Stubs
2022-06-19 improved initialisation
2022-06-19 replaced MPC Wrapper by C++ implementation
2022-06-19 Removed old MPC Py class
2022-06-19 started controller.cpp
2022-06-19 StatePlanner initialises with Params now
2022-06-20 bugfix: added href to shared params interface
2022-06-20 removed redundant class
2022-06-20 adapted interface of controller
2022-06-20 adapted interface
2022-06-20 estimator takes baseorientation as RPY now
2022-06-20 BugFix: body rotation has been ignored in feet position calculation
2022-06-20 using footstepplanners gain from param configuration
2022-06-20 replaced Gait::getCurrentGait by matrix
2022-06-20 baseorientation is RPY instead of quaternion now
2022-06-20 first commit of controller.cpp
2022-06-20 removed global variables from MPCController
2022-06-21 unified urdf consumption
2022-06-21 fixed initialisation of Controller.cpp
2022-06-21 implement input from remote to Controller.cpp
2022-06-21 implemented gait update in Controller.cpp
2022-06-23 checked footTrajectorygenerator
2022-06-23 bugfix:: missing base_targets
2022-06-23 controller.cpp
2022-06-24 bugfix in footgenerator
2022-06-24 Bugfix: Params to WBC were swapped :-(
2022-06-24 added error message
2022-06-24 tuned
2022-06-24 walking straight works now, working in circles not yet
2022-06-25 BugFix: wrong body rotation in feet computation
2022-06-25 moved pyb from controller.py in main.py
2022-06-25 introduced gait for Controller.cpp
2022-06-25 Fixed PY gait change
2022-06-25 Bugfix: Remove remotecontrol logic from PY controller
2022-06-25 Fxied gait change in Cpp
2022-06-25 removed unused members
2022-06-25 Cleaned up
2022-06-25 created test scenario for rotation on the spot
2022-06-25 BUGFIX: cross product in feet target computation had the wrong sign
2022-06-25 Damping was too low, is now 0.2
2022-06-26 prepared MPC controller for faster runs
2022-06-26 Made InvKin Eigen types fixed
2022-06-26 made some Eigen types in WBC fixed
2022-06-26 speed up of compiler
2022-06-26 replaced dynamic Eigen types by fixed ones
2022-06-26 Use of fixed Eigen types
2022-06-26 used fixed Eigen types in Stateplanner
2022-06-26 code cleanup
2022-06-26 gave MPC and WBC proper names
2022-06-26 new function delay_us
2022-06-26 mae PY and C++ sync
2022-06-26 tidy up
2022-06-26 simplified result of MPC
2022-06-26 use of fixed Eigen types in FootStepPlanner
2022-06-26 more fixed Eigen types
2022-06-26 even more fixed types
2022-06-26 Bugfix: MPC result matrix dims were wrong
2022-06-26 MPC takes CoM offset now from computation instead of setting
2022-06-26 BUGFIX: CoM_offset was missing in python stub
2022-06-26 replaced hard coded footstep positions by computation
2022-06-26 replaced hardcoded inertia by computation
2022-06-26 added collision model (not yet evaluated though)
2022-06-27 no message
2022-06-27 docs
2022-06-27 index on (no branch): a5c248f docs
2022-06-27 IMU docs
2022-06-28 sphynx
2022-06-28 sphync
2022-06-28 doc structure
2022-06-28 first image
2022-06-28 IMU cable
2022-06-28 imu to USB
2022-06-28 Connected new Microstrain IMU
2022-06-28 forgot some files...
2022-06-29 IMU video
2022-06-29 try to autopolay
2022-06-29 another try for autoplay
2022-06-29 ok, with a giphy it's working
2022-06-29 introduced EKF
2022-06-29 First version of UKF
2022-06-29 now with code
2022-06-30 reorg
2022-06-30 Created class unscented kalman filter
2022-06-30 clean up code
2022-06-30 removed global variables
2022-07-01 added magnetssensor
2022-07-01 added timeout to Magnetometer reading
2022-07-01 added Magnetometer to UKF
2022-07-01 added 3.3V power supply
2022-07-01 Added Standby Line for 3.3. power supply
2022-07-01 removed redundant param members as preparationfor dynamic dt_mpc change
2022-07-01 remove redundant parameter members
2022-07-01 remove param members
2022-07-02 prepared Gait cleanup
2022-07-02 reduced code
2022-07-02 removed redundant T_mpc
2022-07-02 added N_steps param
2022-07-02 removed gait from params
2022-07-02 removed v_switch and t_switch
2022-07-02 massive code cleanup
2022-07-02 made gait more compact and added N_period
2022-07-02 removed N_DEBUG and added N_period to MPC
2022-07-02 N_period > 1 is working now
2022-07-02 nicer
2022-07-02 Magnetometer works
2022-07-02 Magnetometer works with interrupt now
2022-07-03 Blindly coded hard iron calibration and north calibration
2022-07-03 aligned axes of magnetometer with IMU
2022-07-03 IMU Holder
2022-07-04 integrated Magnetometer into IMU Manager
2022-07-07 rename StagePlanner to BodyPlanner
2022-07-07 proper naming
2022-07-07 Fixed calibration and storage in EEPROM
2022-07-07 IMU returns quaternion + euler now
2022-07-07 Fixed Serial line of IMU
2022-07-07 fixed socket of IMU layout
2022-07-08 Fusion with Magnetometer works
2022-07-08 docu
2022-07-08 Fixed hard iron magnetometer
2022-07-08 improved linear acceleration (but does not work properly yet, still contains tilt)
2022-07-09 IMU Holder
2022-07-09 Rounded body
2022-07-10 Aligned Head
2022-07-11 new power supply
2022-07-11 typo
2022-07-11 better startup
2022-07-11 simplified code
2022-07-11 removed unnecessary transformation matrix
2022-07-12 removed unnecessary API from Complemantaryfilter
2022-07-12 simplified
2022-07-12 added k maintenance
2022-07-12 exposed k maintenance
2022-07-12 added loop counter
2022-07-12 added gait to estimator
2022-07-12 added k to params
2022-07-12 removed parameter
2022-07-12 removed k as parameter, is part of Params now
2022-07-12 removed legacy code
2022-07-15 implemented linear acceleration
2022-07-15 dpoc
2022-07-16 documented code
2022-07-16 equation
2022-07-21 New tail
2022-07-21 bugfix get MPCs result
2022-07-21 reimplemented computation of filter cut off frequency
2022-07-21 tuned timeing
2022-07-21 started new cerebellar board
2022-07-21 forgot files
2022-07-21 added customs.css to conf.py
2022-07-21 new theme
2022-07-21 theme
2022-07-21 sphynxdoc theme
2022-07-22 improved table
2022-07-22 UKF algo
2022-07-22 Schematics with power supply and INA works
2022-07-22 MOSFET Driver tested
2022-07-22 new schematics layout
2022-07-22 buffersize in UART7 for less checksum errors
2022-07-22 new layout
2022-07-22 bizstyle
2022-07-23 Added LED Power Manager
2022-07-23 docs magnetometer
2022-07-23 images magnetometer
2022-07-23 magnetometer docs
2022-07-23 layout
2022-07-23 improved schmeatics
2022-07-25 started Raspi
2022-07-25 portability
2022-07-25 raspi
2022-07-26 It runs on a Raspberry now!
2022-07-26 dealing with PAT
2022-07-26 removed unnecessary parts in cmake
2022-07-26 more removals...
2022-07-26 activated MPC again
2022-07-26 Started KeyboardListener
2022-07-27 new PAT
2022-07-27 started main programm in C++
2022-07-28 tuning & new parameter enable_early_mpc_result
2022-07-28 beautified
2022-07-28 removed redundant functions
2022-07-28 Main Board V3 with 5V 3A power supply for Raspberry
2022-07-29 restart ODrive
2022-07-30 Ordered PCB V1.2
2022-07-31 Display is now connected to Raspi instead of Teensy
